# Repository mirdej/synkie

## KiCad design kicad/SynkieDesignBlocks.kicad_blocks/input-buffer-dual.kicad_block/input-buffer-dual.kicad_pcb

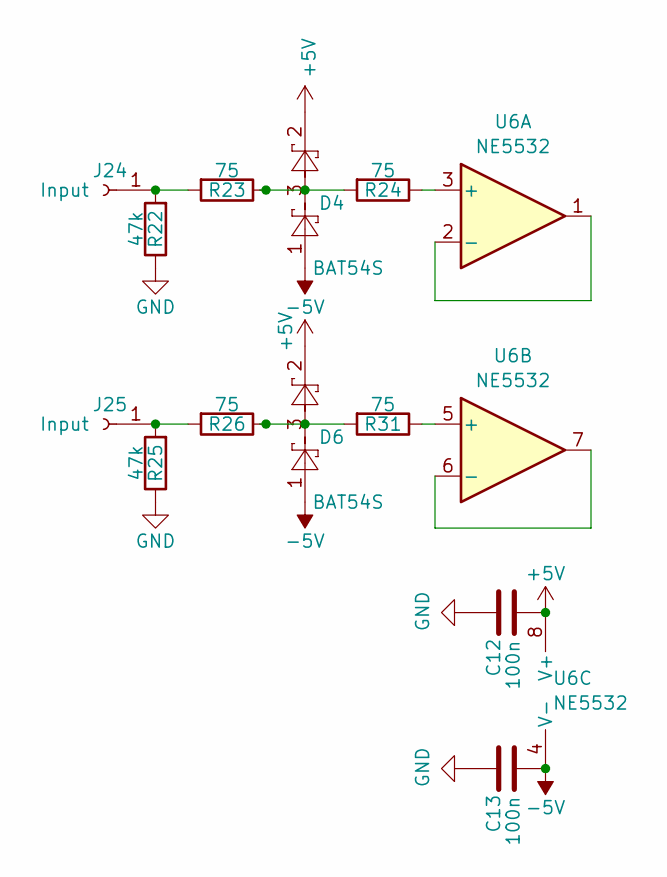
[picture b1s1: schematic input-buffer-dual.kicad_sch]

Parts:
C12, C13: 100n; C_0603_1608Metric; LCSC C14663
D4, D6: BAT54S; SOT-23; LCSC C8592
J24, J25: Input; Banana2mm-Löthülse
R22, R25: 47k; R_0603_1608Metric; LCSC C25819
R23, R24, R26, R31: 75; R_0603_1608Metric; LCSC C4275
U6: NE5532; SOIC-8_3.9x4.9mm_P1.27mm; LCSC C7426

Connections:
+5V: C12.2, D4.2, D6.2, U6.8 (V+)
-5V: C13.2, D4.1, D6.1, U6.4 (V-)
GND: C12.1, C13.1, R22.1, R25.1
unnamed: D4.3, R23.1, R24.2
unnamed: D6.3, R26.1, R31.2
unnamed: J24.1 (Pin_1_1), R22.2, R23.2
unnamed: J25.1 (Pin_1_1), R25.2, R26.2
unnamed: R24.1, U6.3 (+)
unnamed: U6.1, U6.2 (-)
unnamed: R31.1, U6.5 (+)
unnamed: U6.6 (-), U6.7

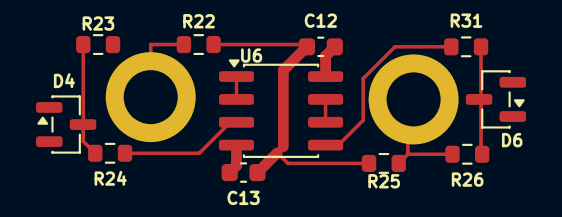
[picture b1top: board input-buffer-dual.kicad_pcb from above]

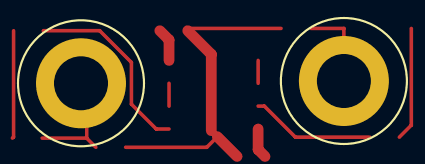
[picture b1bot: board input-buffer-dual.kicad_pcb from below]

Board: 2 copper layers, 13 parts (2 on the bottom side), 11 nets.

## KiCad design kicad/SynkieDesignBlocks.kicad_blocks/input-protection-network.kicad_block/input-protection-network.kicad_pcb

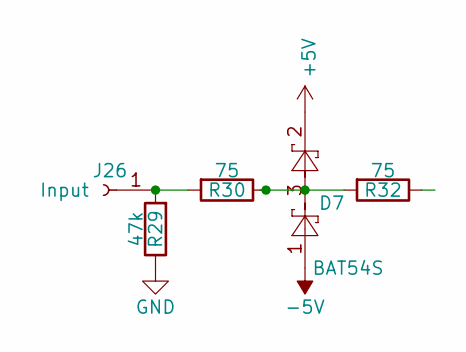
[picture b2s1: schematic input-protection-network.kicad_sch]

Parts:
D7: BAT54S; SOT-23; LCSC C8592
J26: Input; Banana2mm-Löthülse
R29: 47k; R_0603_1608Metric; LCSC C25819
R30, R32: 75; R_0603_1608Metric; LCSC C4275

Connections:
+5V: D7.2
-5V: D7.1
GND: R29.1
unnamed: D7.3, R30.1, R32.2
unnamed: J26.1 (Pin_1_1), R29.2, R30.2

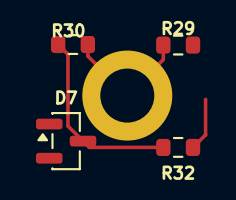
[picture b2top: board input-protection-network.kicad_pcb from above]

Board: 2 copper layers, 5 parts (1 on the bottom side), 2 nets.

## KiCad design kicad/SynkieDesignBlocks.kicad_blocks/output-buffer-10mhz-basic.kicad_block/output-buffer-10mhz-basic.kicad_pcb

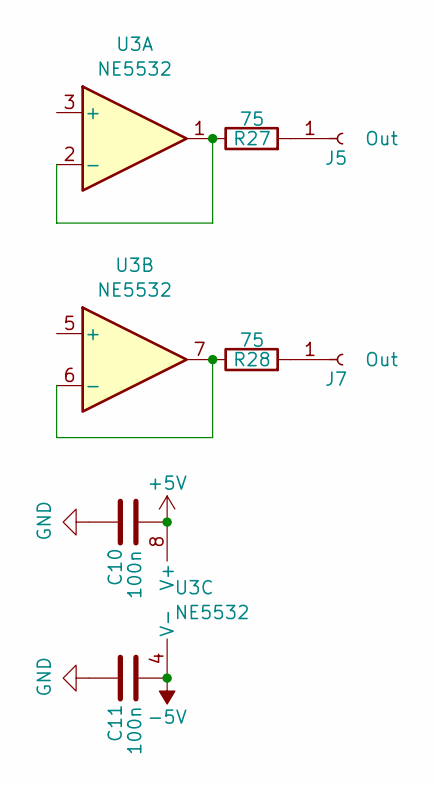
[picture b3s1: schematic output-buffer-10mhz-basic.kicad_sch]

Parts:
C10, C11: 100n; C_0603_1608Metric; LCSC C14663
J5, J7: Out; Banana2mm-Löthülse
R27, R28: 75; R_0603_1608Metric; LCSC C4275
U3: NE5532; SOIC-8_5.3x5.3mm_P1.27mm; LCSC C7426

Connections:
+5V: C10.2, U3.8 (V+)
-5V: C11.2, U3.4 (V-)
GND: C10.1, C11.1
unnamed: J5.1 (Pin_1_1), R27.2
unnamed: J7.1 (Pin_1_1), R28.2
unnamed: R27.1, U3.1, U3.2 (-)
unnamed: R28.1, U3.6 (-), U3.7

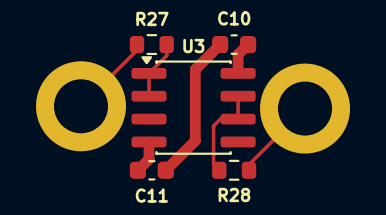
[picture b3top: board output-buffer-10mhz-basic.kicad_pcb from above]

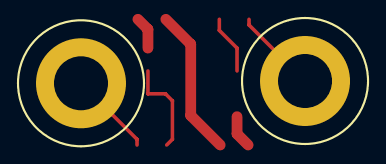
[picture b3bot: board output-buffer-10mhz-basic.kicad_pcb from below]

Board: 2 copper layers, 7 parts (2 on the bottom side), 7 nets.

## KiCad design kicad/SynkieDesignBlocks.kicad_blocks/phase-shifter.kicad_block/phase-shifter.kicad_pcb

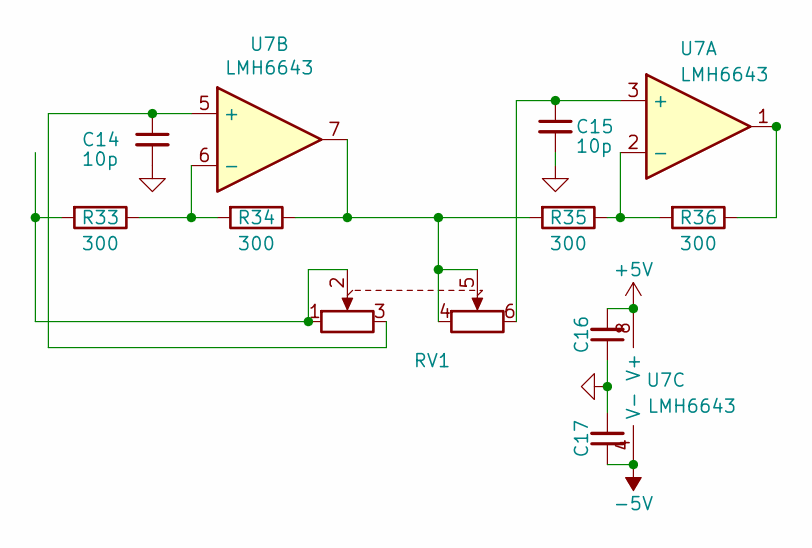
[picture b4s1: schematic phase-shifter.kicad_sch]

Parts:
C14, C15: 10p; C_0603_1608Metric; LCSC C1634
C16, C17: 100n; C_0402_1005Metric; LCSC C1525
R33, R34, R35, R36: 300; R_0603_1608Metric; LCSC C23025
RV1: RK12L123
U7: LMH6643; VSSOP-8_3x3mm_P0.65mm; LCSC C478382

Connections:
+5V: C16.2, U7.8 (V+)
-5V: C17.1, U7.4 (V-)
GND: C14.2, C15.2, C16.1, C17.2
unnamed: R33.2, RV1.1, RV1.2
unnamed: R36.1, U7.1
unnamed: R34.1, R35.2, RV1.4, RV1.5, U7.7
unnamed: C15.1, RV1.6, U7.3 (+)
unnamed: R35.1, R36.2, U7.2 (-)
unnamed: C14.1, RV1.3, U7.5 (+)
unnamed: R33.1, R34.2, U7.6 (-)

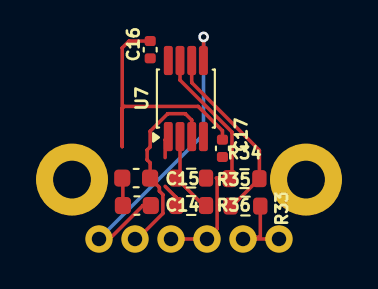
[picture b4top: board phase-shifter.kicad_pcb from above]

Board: 2 copper layers, 10 parts (1 on the bottom side), 10 nets.

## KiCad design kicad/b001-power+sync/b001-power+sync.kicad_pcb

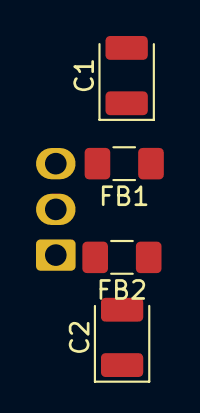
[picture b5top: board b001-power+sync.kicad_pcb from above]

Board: 2 copper layers, 5 parts (1 on the bottom side), 5 nets, no tracks yet.

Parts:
C1, C2: 10u; CP_EIA-3528-21_Kemet-B
FB1, FB2: Ferrite_Bead; L_1206_3216Metric_Pad1.42x1.75mm_HandSolder
J1: Supply; Molex_KK-254_AE-6410-03A_1x03_P2.54mm_Vertical

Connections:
+5V: C1.1, FB1.1
-5V: C2.2, FB2.1
GND: C1.2, C2.1, J1.2
unnamed: FB1.2, J1.3
unnamed: FB2.2, J1.1

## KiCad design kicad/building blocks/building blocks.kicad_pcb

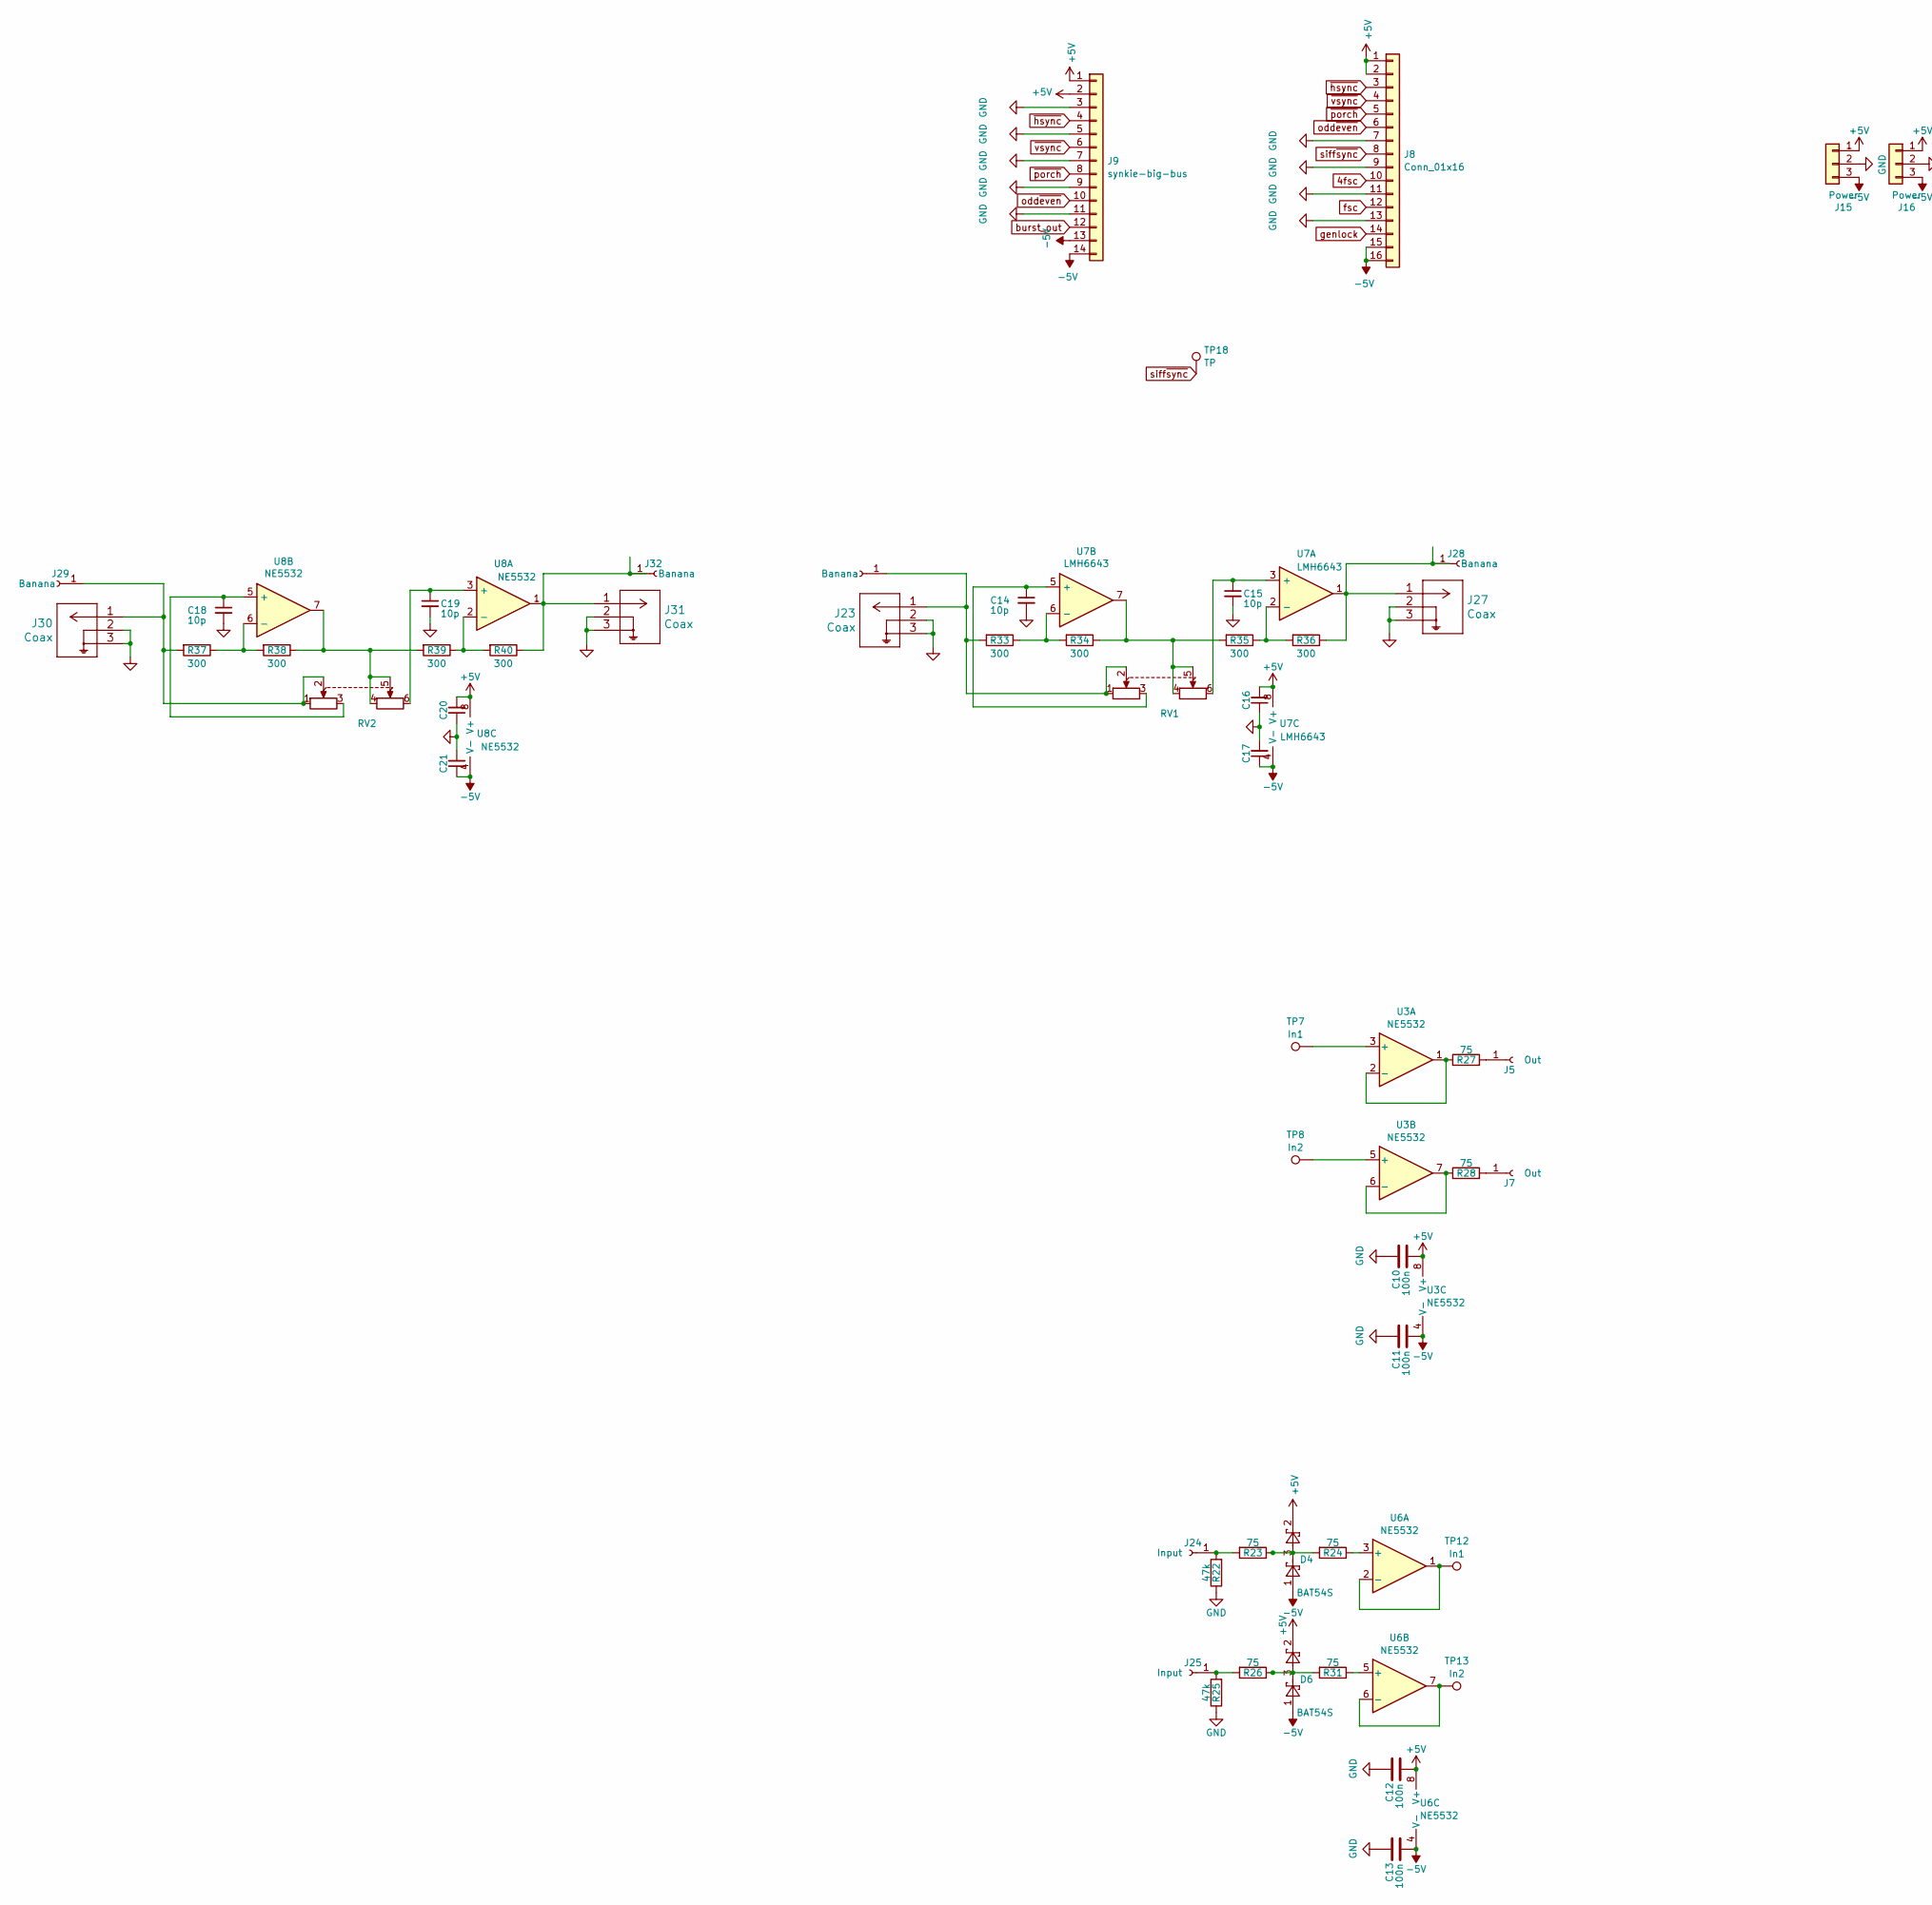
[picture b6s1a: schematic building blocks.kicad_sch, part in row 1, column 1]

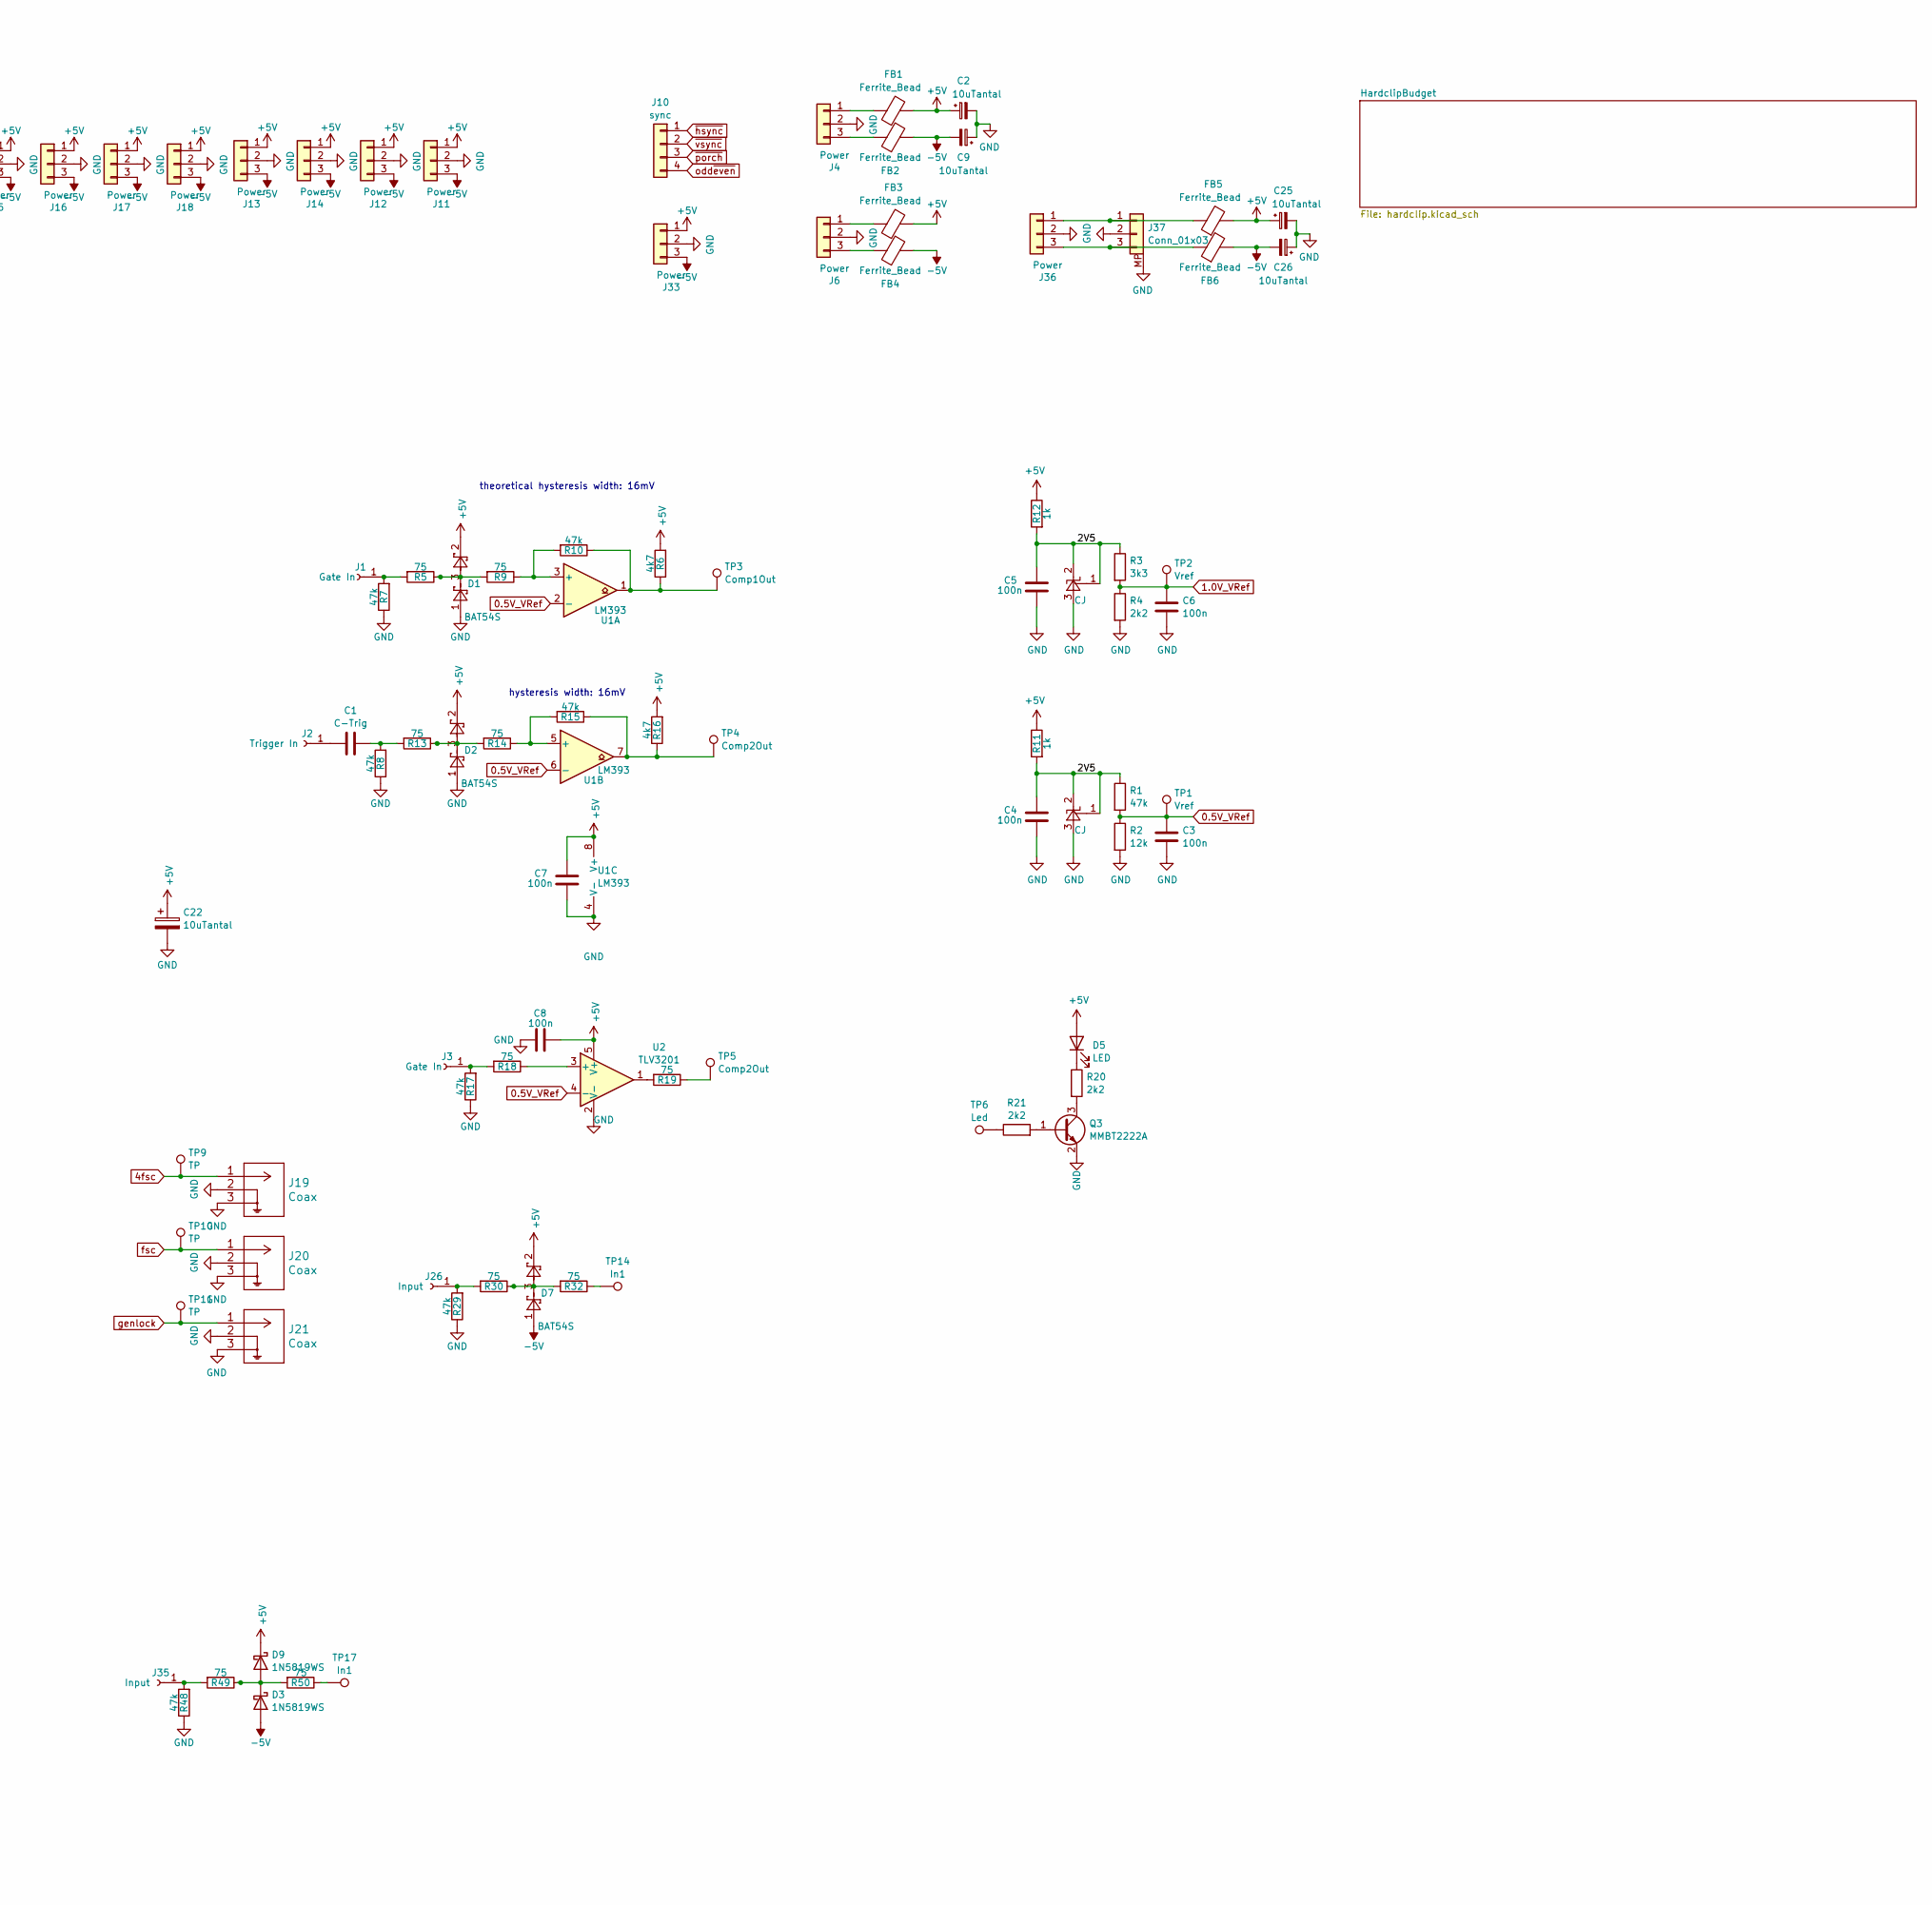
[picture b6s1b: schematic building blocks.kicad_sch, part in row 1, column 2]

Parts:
C1: C-Trig; C_0805_2012Metric
C2, C9, C22, C25, C26: 10uTantal; CP_EIA-3216-18_Kemet-A; LCSC C7171
C3, C4, C5, C6, C7, C8, C10, C11, C12, C13: 100n; C_0603_1608Metric; LCSC C14663
C14, C15, C18, C19: 10p; C_0603_1608Metric; LCSC C1634
C16, C17, C20, C21: 100n; C_0402_1005Metric; LCSC C1525
D1, D2, D4, D6, D7: BAT54S; SOT-23; LCSC C8592
D3, D9: 1N5819WS; D_SOD-323; LCSC C191023
D5: LED; LED_1206_3216Metric_ReverseMount_Hole1.8x2.4mm; LCSC C125108
FB1, FB2, FB3, FB4, FB5, FB6: Ferrite_Bead; L_0805_2012Metric; LCSC C1017
J1, J3: Gate In; TestPoint_THTPad_D4.0mm_Drill2.0mm
J2: Trigger In; TestPoint_THTPad_D4.0mm_Drill2.0mm
J4, J33: Power; Molex_KK-254_AE-6410-03A_1x03_P2.54mm_Vertical
J5, J7: Out; TestPoint_THTPad_D4.0mm_Drill2.0mm
J6, J11, J12, J13, J14, J15, J16, J17, J18: Power; Molex_PicoBlade_53398-0371_1x03-1MP_P1.25mm_Vertical; LCSC C293633
J8: Conn_01x16; IDC-Header_2x08_P2.54mm_Vertical
J9: synkie-big-bus; IDC-Header_2x07_P2.54mm_Vertical
J10: sync; Molex_KK-254_AE-6410-04A_1x04_P2.54mm_Vertical
J19, J20, J21, J23, J27, J30, J31: Coax; TE_UMCC_2337019-1; LCSC C5137195
J22, J28, J29, J32: Banana; TestPoint_THTPad_D4.0mm_Drill2.0mm
J24, J25, J26, J35: Input; TestPoint_THTPad_D4.0mm_Drill2.0mm
J36: Power; Molex_KK-254_AE-6410-03A_1x03_P2.54mm_Vertical_SMD
J37: Conn_01x03; Molex_PicoBlade_53398-0371_1x03-1MP_P1.25mm_Vertical; LCSC C293633
Q3: MMBT2222A; SOT-23; LCSC C8512
R1, R7, R8, R10, R15, R17, R22, R25, R29, R48: 47k; R_0603_1608Metric; LCSC C25819
R2: 12k; R_0603_1608Metric; LCSC C22790
R3: 3k3; R_0603_1608Metric; LCSC C22978
R4, R20, R21: 2k2; R_0603_1608Metric; LCSC C4190
R5, R9, R13, R14, R18, R19, R23, R24, R26, R27, R28, R30, R31, R32, R49, R50: 75; R_0603_1608Metric; LCSC C4275
R6, R16: 4k7; R_0603_1608Metric; LCSC C23162
R11, R12: 1k; R_0603_1608Metric; LCSC C21190
R33, R34, R35, R36, R37, R38, R39, R40: 300; R_0603_1608Metric; LCSC C23025
RV1, RV2: PRS12R-2
TP1, TP2: Vref; TestPoint_THTPad_D4.0mm_Drill2.0mm
TP3: Comp1Out; TestPoint_THTPad_D4.0mm_Drill2.0mm
TP4, TP5: Comp2Out; TestPoint_THTPad_D4.0mm_Drill2.0mm
TP6: Led; TestPoint_THTPad_D4.0mm_Drill2.0mm
TP7, TP12, TP14, TP17: In1; TestPoint_THTPad_D4.0mm_Drill2.0mm
TP8, TP13: In2; TestPoint_THTPad_D4.0mm_Drill2.0mm
TP9, TP10, TP11, TP18: TP; TestPoint_THTPad_D4.0mm_Drill2.0mm
U1: LM393; SOIC-8_3.9x4.9mm_P1.27mm; LCSC C7955
U2: TLV3201; SOT-23-5; LCSC C105188
U3, U6, U8: NE5532; SOIC-8_3.9x4.9mm_P1.27mm; LCSC C7426
U4, U5: CJ; SOT-23; LCSC C3113
U7: LMH6643; VSSOP-8_3x3mm_P0.65mm; LCSC C478382

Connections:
0.5V_VRef: C3.1, R1.2, R2.1, TP1.1 (1_1), U1.2 (-), U1.6 (-), U2.4 (-)
1.0V_VRef: C6.1, R3.2, R4.1, TP2.1 (1_1); also elsewhere on the board
4fsc: J8.10, J19.1, TP9.1 (1_1)
+5V: C2.1, C7.1, C8.2, C10.2, C12.2, C16.2, C20.2, C22.1, C25.1, D1.2, D2.2, D4.2, D5.2 (A), D6.2, D7.2, D9.1 (K), FB1.2, FB3.2, FB5.2, J8.1, J8.2, J9.1, J9.2, J11.1, J12.1, J13.1, J14.1, J15.1, J16.1, J17.1, J18.1, J33.1, R6.2, R11.1, R12.1, R16.2, U1.8 (V+), U2.5 (V+), U3.8 (V+), U6.8 (V+), U7.8 (V+), U8.8 (V+); also elsewhere on the board
-5V: C9.2, C11.2, C13.2, C17.1, C21.1, C26.2, D3.2 (A), D4.1, D6.1, D7.1, FB2.2, FB4.2, FB6.2, J8.15, J8.16, J9.13, J9.14, J11.3, J12.3, J13.3, J14.3, J15.3, J16.3, J17.3, J18.3, J33.3, U3.4 (V-), U6.4 (V-), U7.4 (V-), U8.4 (V-); also elsewhere on the board
/2V5: C4.1, C5.1, R1.1, R3.1, R11.2, R12.2, U4.1 (R), U4.2 (K), U5.1 (R), U5.2 (K)
GND: C2.2, C3.2, C4.2, C5.2, C6.2, C7.2, C8.1, C9.1, C10.1, C11.1, C12.1, C13.1, C14.2, C15.2, C16.1, C17.2, C18.2, C19.2, C20.1, C21.2, C22.2, C25.2, C26.1, D1.1, D2.1, J4.2, J6.2, J8.7, J8.9, J8.11, J8.13, J9.3, J9.5, J9.7, J9.9, J9.11, J11.2, J12.2, J13.2, J14.2, J15.2, J16.2, J17.2, J18.2, J19.2, J19.3, J20.2, J20.3, J21.2, J21.3, J23.2, J23.3, J27.2, J27.3, J30.2, J30.3, J31.2, J31.3, J33.2, J36.2, J37.2, J37.MP, Q3.2 (E), R2.2, R4.2, R7.1, R8.1, R17.1, R22.1, R25.1, R29.1, R48.1, U1.4 (V-), U2.2 (V-), U4.3 (A), U5.3 (A); also elsewhere on the board
unnamed: C1.2, R8.2, R13.2
unnamed: D1.3, R5.1, R9.2
unnamed: D2.3, R13.1, R14.2
unnamed: D3.1 (K), D9.2 (A), R49.1, R50.2
unnamed: D4.3, R23.1, R24.2
unnamed: D5.1 (K), R20.1
unnamed: D6.3, R26.1, R31.2
unnamed: D7.3, R30.1, R32.2
unnamed: J1.1 (Pin_1_1), R5.2, R7.2
unnamed: C1.1, J2.1 (Pin_1_1)
unnamed: J3.1 (Pin_1_1), R17.2, R18.2
unnamed: FB1.1, J4.1
unnamed: FB2.1, J4.3
unnamed: J5.1 (Pin_1_1), R27.2
unnamed: FB3.1, J6.1
unnamed: FB4.1, J6.3
unnamed: J7.1 (Pin_1_1), R28.2
unnamed: J22.1 (Pin_1_1), J23.1, R33.2, RV1.1, RV1.2
unnamed: J24.1 (Pin_1_1), R22.2, R23.2
unnamed: J25.1 (Pin_1_1), R25.2, R26.2
unnamed: J26.1 (Pin_1_1), R29.2, R30.2
unnamed: J27.1, J28.1 (Pin_1_1), R36.1, U7.1
unnamed: J29.1 (Pin_1_1), J30.1, R37.2, RV2.1, RV2.2
unnamed: J31.1, J32.1 (Pin_1_1), R40.1, U8.1
unnamed: J35.1 (Pin_1_1), R48.2, R49.2
unnamed: FB5.1, J36.1, J37.1
unnamed: FB6.1, J36.3, J37.3
unnamed: Q3.1 (B), R21.2
unnamed: Q3.3 (C), R20.2
unnamed: R6.1, R10.1, TP3.1 (1_1), U1.1
unnamed: R15.1, R16.1, TP4.1 (1_1), U1.7
unnamed: R19.1, TP5.1 (1_1)
unnamed: R19.2, U2.1
unnamed: R21.1, TP6.1 (1_1)
unnamed: R32.1, TP14.1 (1_1)
unnamed: R34.1, R35.2, RV1.4, RV1.5, U7.7
unnamed: R38.1, R39.2, RV2.4, RV2.5, U8.7
unnamed: R50.1, TP17.1 (1_1)
unnamed: R9.1, R10.2, U1.3 (+)
unnamed: R14.1, R15.2, U1.5 (+)
unnamed: R18.1, U2.3 (+)
unnamed: TP7.1 (1_1), U3.3 (+)
unnamed: R27.1, U3.1, U3.2 (-)
unnamed: TP8.1 (1_1), U3.5 (+)
unnamed: R28.1, U3.6 (-), U3.7
unnamed: R24.1, U6.3 (+)
unnamed: TP12.1 (1_1), U6.1, U6.2 (-)
unnamed: R31.1, U6.5 (+)
unnamed: TP13.1 (1_1), U6.6 (-), U6.7
unnamed: C15.1, RV1.6, U7.3 (+)
unnamed: R35.1, R36.2, U7.2 (-)
unnamed: C14.1, RV1.3, U7.5 (+)
unnamed: R33.1, R34.2, U7.6 (-)
unnamed: C19.1, RV2.6, U8.3 (+)
unnamed: R39.1, R40.2, U8.2 (-)
unnamed: C18.1, RV2.3, U8.5 (+)
unnamed: R37.1, R38.2, U8.6 (-)
burst_out: J9.12
fsc: J8.12, J20.1, TP10.1 (1_1)
genlock: J8.14, J21.1, TP11.1 (1_1)
odd~even: J8.6, J9.10, J10.4
siff~sync: J8.8, TP18.1 (1_1)
~hsync: J8.3, J9.4, J10.1
~porch: J8.5, J9.8, J10.3
~vsync: J8.4, J9.6, J10.2

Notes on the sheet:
hysteresis width: 16mV
theoretical hysteresis width: 16mV

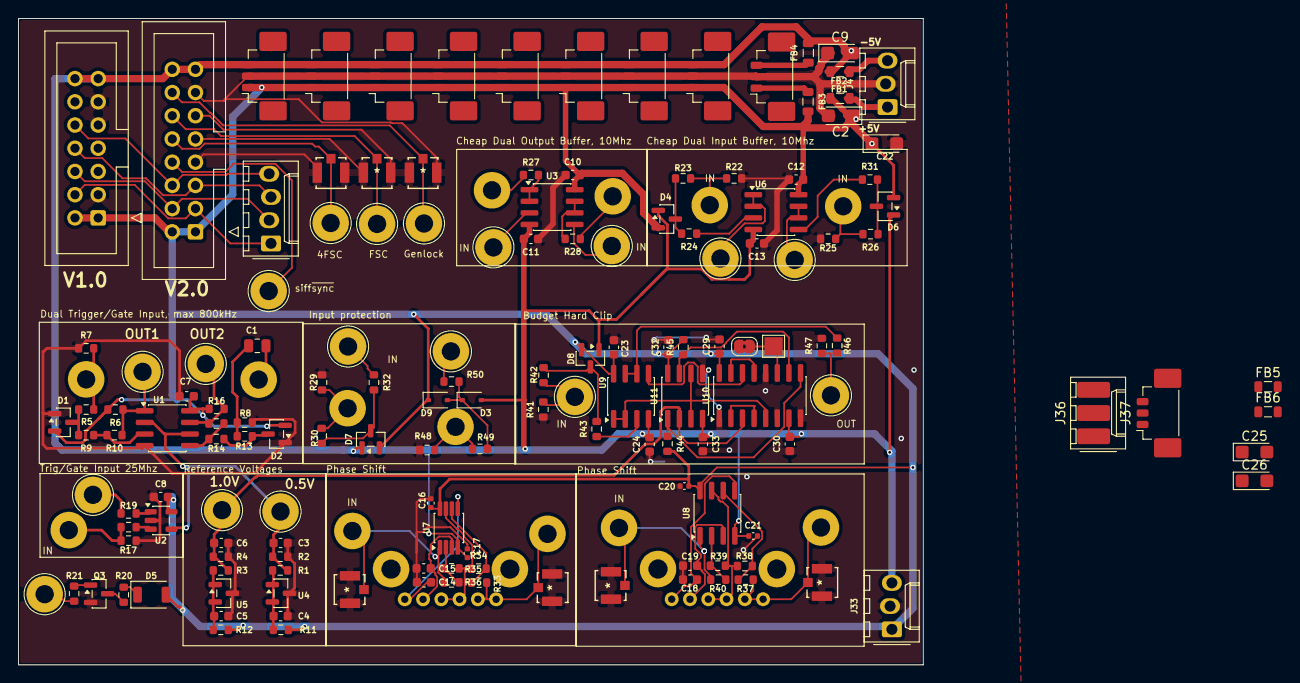
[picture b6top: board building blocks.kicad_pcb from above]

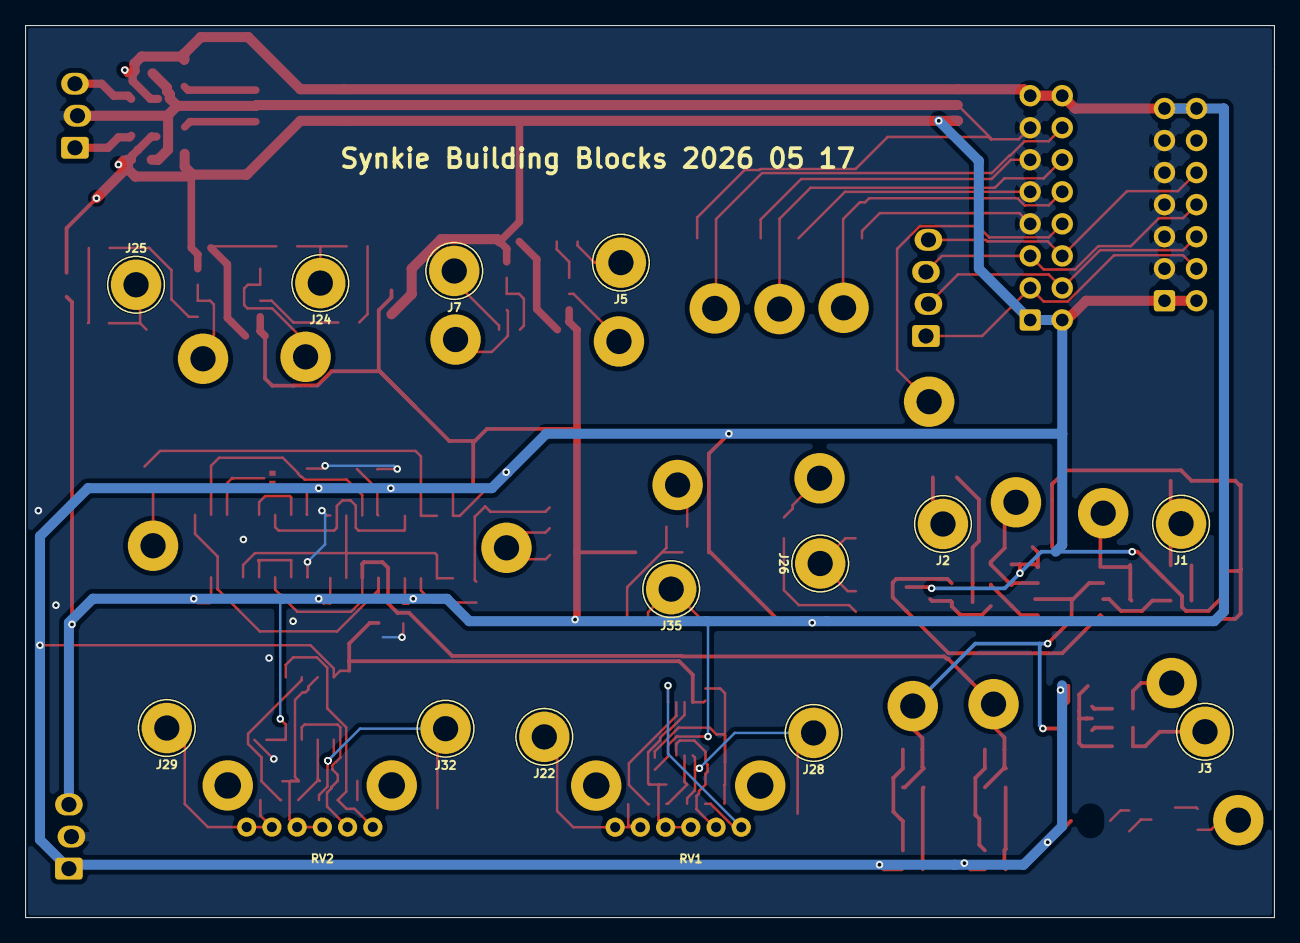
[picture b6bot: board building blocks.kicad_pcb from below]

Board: 2 copper layers, 99.0 x 70.7 mm, 165 parts (15 on the bottom side), 83 nets.

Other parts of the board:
C23, C24, C29, C30, C32, C33: 100n; C_0603_1608Metric
D8: BAT54S; SOT-23
J34: Input; TestPoint_THTPad_D4.0mm_Drill2.0mm
JP1: Jumper_2_Bridged; SolderJumper-2_P1.3mm_Bridged2Bar_RoundedPad1.0x1.5mm
R41: 47k; R_0603_1608Metric
R42, R43: 75; R_0603_1608Metric
R44, R45: 6k8; R_0603_1608Metric
R46: 4k7; R_0603_1608Metric
R47: 12k; R_0603_1608Metric
TP15: TP; TestPoint_THTPad_D4.0mm_Drill2.0mm
TP16: TestPoint; TestPoint_Pad_2.0x2.0mm
U9: NE5532; SOIC-8_3.9x4.9mm_P1.27mm
U10: TPW4053-SR; SOIC-16_3.9x9.9mm_P1.27mm
U11: LM393; SOIC-8_3.9x4.9mm_P1.27mm

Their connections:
1.0V_VRef: U10.3 (Z1), U11.2 (-); also elsewhere on the board
+5V: C23.2, C29.1, C32.1, D8.2, R44.2, R45.2, U9.8 (V+), U10.16 (VDD), U11.8 (V+); also elsewhere on the board
-5V: C24.2, C30.2, C33.1, D8.1, U9.4 (V-), U10.7 (VEE), U11.4 (V-); also elsewhere on the board
/HardclipBudget/out: R46.1, R47.1, TP15.1 (1_1)
GND: C23.1, C24.1, C29.2, C30.1, C32.2, C33.2, R41.1, R47.2, U10.1 (Y1), U10.6 (Inh), U10.8 (VSS), U10.12 (X0), U11.5 (+); also elsewhere on the board
unnamed: D8.3, R42.1, R43.2
unnamed: J34.1 (Pin_1_1), R41.2, R42.2
unnamed: JP1.2 (B), TP16.1 (1_1), U10.11 (A)
unnamed: R43.1, U9.3 (+)
unnamed: R46.2, U9.6 (-), U9.7
unnamed: R45.1, U10.10 (B), U11.7
unnamed: R44.1, U10.9 (C), U11.1
unnamed: U10.13 (X1), U10.15 (Y)
unnamed: U9.5 (+), U10.14 (X)
unnamed: U10.2 (Y0), U10.4 (Z)
unnamed: U9.1, U9.2 (-), U10.5 (Z0), U11.3 (+), U11.6 (-)

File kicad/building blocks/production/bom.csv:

Designator,Footprint,Quantity,Value,LCSC Part #
C1,0805,1,C-Trig,
"C10, C11, C12, C13, C23, C24, C29, C3, C30, C32, C33, C4, C5, C6, C7, C8",0603,16,100n,C14663
"C14, C15, C18, C19",0603,4,10p,C1634
"C16, C17, C20, C21",0402,4,100n,C1525 
"C2, C9",0805,2,10u,C15850
C22,CP_EIA-3216-18_Kemet-A,1,10uTantal,C7171
"D1, D2, D4, D6, D7, D8",SOT-23,6,BAT54S,C8592
"D3, D9",D_SOD-323,2,1N5819WS,C191023
D5,1206,1,LED,C125108
"FB1, FB2, FB3, FB4",0805,4,Ferrite_Bead,C1017
"J1, J3",TestPoint_THTPad_D4.0mm_Drill2.0mm,2,Gate In,
J10,Molex_KK-254_AE-6410-04A_1x04_P2.54mm_Vertical,1,sync,
"J11, J12, J13, J14, J15, J16, J17, J18, J6",Molex_PicoBlade_53398-0371_1x03-1MP_P1.25mm_Vertical,9,Power,C293633
"J19, J20, J21, J23, J27, J30, J31",TE_UMCC_2337019-1,7,Coax,C5137195
J2,TestPoint_THTPad_D4.0mm_Drill2.0mm,1,Trigger In,
"J22, J28, J29, J32",TestPoint_THTPad_D4.0mm_Drill2.0mm,4,Banana,
"J24, J25, J26, J34, J35",TestPoint_THTPad_D4.0mm_Drill2.0mm,5,Input,
"J33, J4",Molex_KK-254_AE-6410-03A_1x03_P2.54mm_Vertical,2,Power,
"J5, J7",TestPoint_THTPad_D4.0mm_Drill2.0mm,2,Out,
J8,IDC-Header_2x08_P2.54mm_Vertical,1,Conn_01x16,
JP1,SolderJumper-2_P1.3mm_Bridged2Bar_RoundedPad1.0x1.5mm,1,Jumper_2_Bridged,
Q3,SOT-23,1,MMBT2222A,C8512
"R1, R10, R15, R17, R22, R25, R29, R41, R48, R7, R8",0603,11,47k,C25819
"R11, R12",0603,2,1k,C21190
"R13, R14, R18, R19, R23, R24, R26, R27, R28, R30, R31, R32, R42, R43, R49, R5, R50, R9",0603,18,75,C4275 
"R16, R46, R6",0603,3,4k7,C23162
"R2, R47",0603,2,12k,C22790
"R20, R21, R4",0603,3,2k2,C4190
R3,0603,1,3k3,C22978
"R33, R34, R35, R36, R37, R38, R39, R40",0603,8,300,C23025
"R44, R45",0603,2,6k8,C23212
"RV1, RV2",PRS12R-2,2,~,
"TP1, TP2",TestPoint_THTPad_D4.0mm_Drill2.0mm,2,Vref,
"TP10, TP11, TP15, TP18, TP9",TestPoint_THTPad_D4.0mm_Drill2.0mm,5,TP,
"TP12, TP14, TP17, TP7",TestPoint_THTPad_D4.0mm_Drill2.0mm,4,In1,
"TP13, TP8",TestPoint_THTPad_D4.0mm_Drill2.0mm,2,In2,
TP16,TestPoint_Pad_2.0x2.0mm,1,TestPoint,
TP3,TestPoint_THTPad_D4.0mm_Drill2.0mm,1,Comp1Out,
"TP4, TP5",TestPoint_THTPad_D4.0mm_Drill2.0mm,2,Comp2Out,
TP6,TestPoint_THTPad_D4.0mm_Drill2.0mm,1,Led,
"U1, U11",SOIC-8_3.9x4.9mm_P1.27mm,2,LM393,C7955
U10,SOIC-16_3.9x9.9mm_P1.27mm,1,TPW4053-SR,C7500846
U2,SOT-23-5,1,TLV3201,C105188
"U3, U6, U8, U9",SOIC-8_3.9x4.9mm_P1.27mm,4,NE5532,C7426
"U4, U5",SOT-23,2,CJ,C3113
U7,VSSOP-8_3x3mm_P0.65mm,1,LMH6643,C478382

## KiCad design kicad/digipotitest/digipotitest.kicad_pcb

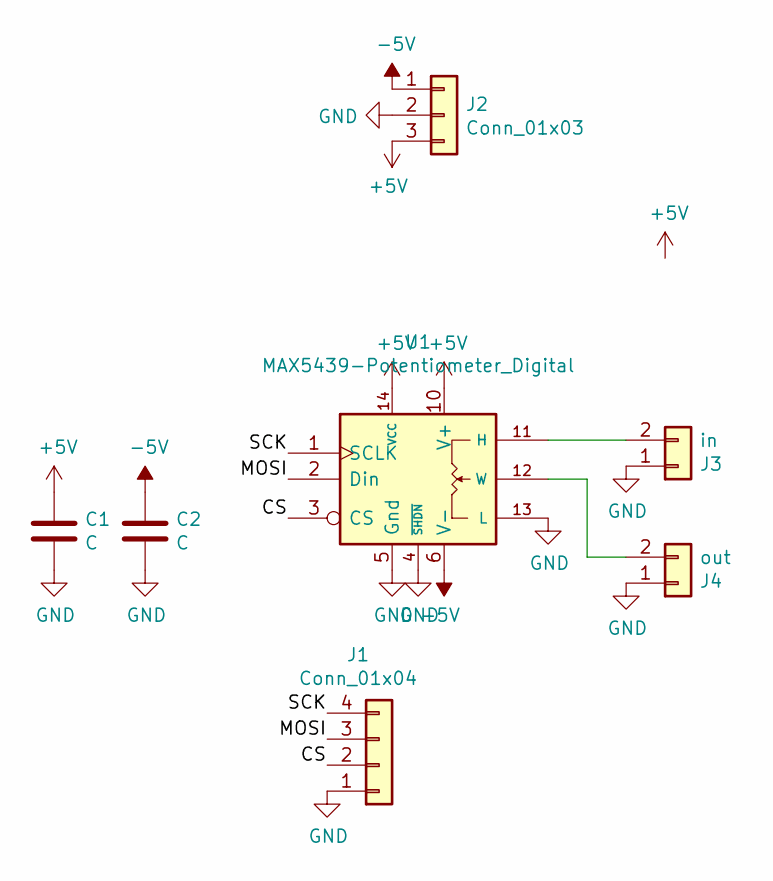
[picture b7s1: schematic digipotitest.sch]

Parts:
C1, C2: C; C_0603_1608Metric_Pad1.05x0.95mm_HandSolder
J1: Conn_01x04; Molex_KK-254_AE-6410-04A_1x04_P2.54mm_Vertical
J2: Conn_01x03; Molex_KK-254_AE-6410-03A_1x03_P2.54mm_Vertical
J3: in; Molex_KK-254_AE-6410-02A_1x02_P2.54mm_Vertical
J4: out; Molex_KK-254_AE-6410-02A_1x02_P2.54mm_Vertical
U1: MAX5439-Potentiometer_Digital; TSSOP-14_4.4x5mm_P0.65mm

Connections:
+5V: C1.1, J2.3, U1.10 (V+), U1.14 (VCC)
-5V: C2.1, J2.1, U1.6 (V-)
/CS: J1.2, U1.3 (CS)
/MOSI: J1.3, U1.2 (Din)
/SCK: J1.4, U1.1 (SCLK)
GND: C1.2, C2.2, J1.1, J2.2, J3.1, J4.1, U1.4 (~SHDN), U1.5 (Gnd), U1.13 (L)
unnamed: J3.2, U1.11 (H)
unnamed: J4.2, U1.12 (W)

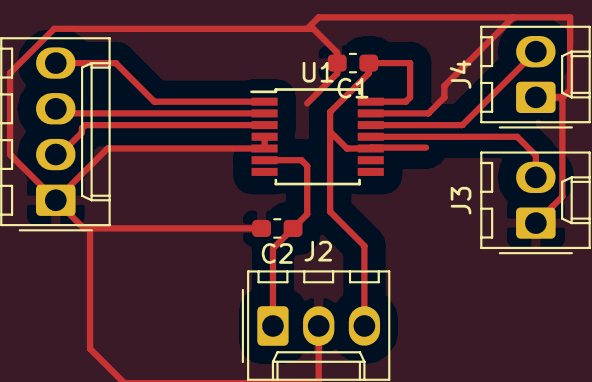
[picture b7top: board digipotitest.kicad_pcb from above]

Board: 2 copper layers, 7 parts (0 on the bottom side), 8 nets.

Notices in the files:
parts and their libraries:
Copyright 2016 Accelerated Designs. All rights reserved.
